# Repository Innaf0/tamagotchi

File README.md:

# tamagotchi
I made a tamagotchi using a guide so i wouldnt really call it my own, if anyone doesnt know whats a tamagotchi i suggest u look it up or in short a tamagotchi is a virtual pet which u have to feed and play with or else it'll get sad just like with real life pets:D
I made this tamagotchi Jinx inspired bc i really like Arcane, my pcb and case both have Jinx inspired drawings

and here's the rendered case which will be transparent so my art could be seen:3

heres my ZINE page

I made this project to learn the basics of hardware
this is my very first hardware project so thats why i decided to follow a guide instead of straight up jumping in to smth i didnt even know how to handle, this is my 2nd or maybe 3rd read.me so tbh idk if this is any good but anyways;)

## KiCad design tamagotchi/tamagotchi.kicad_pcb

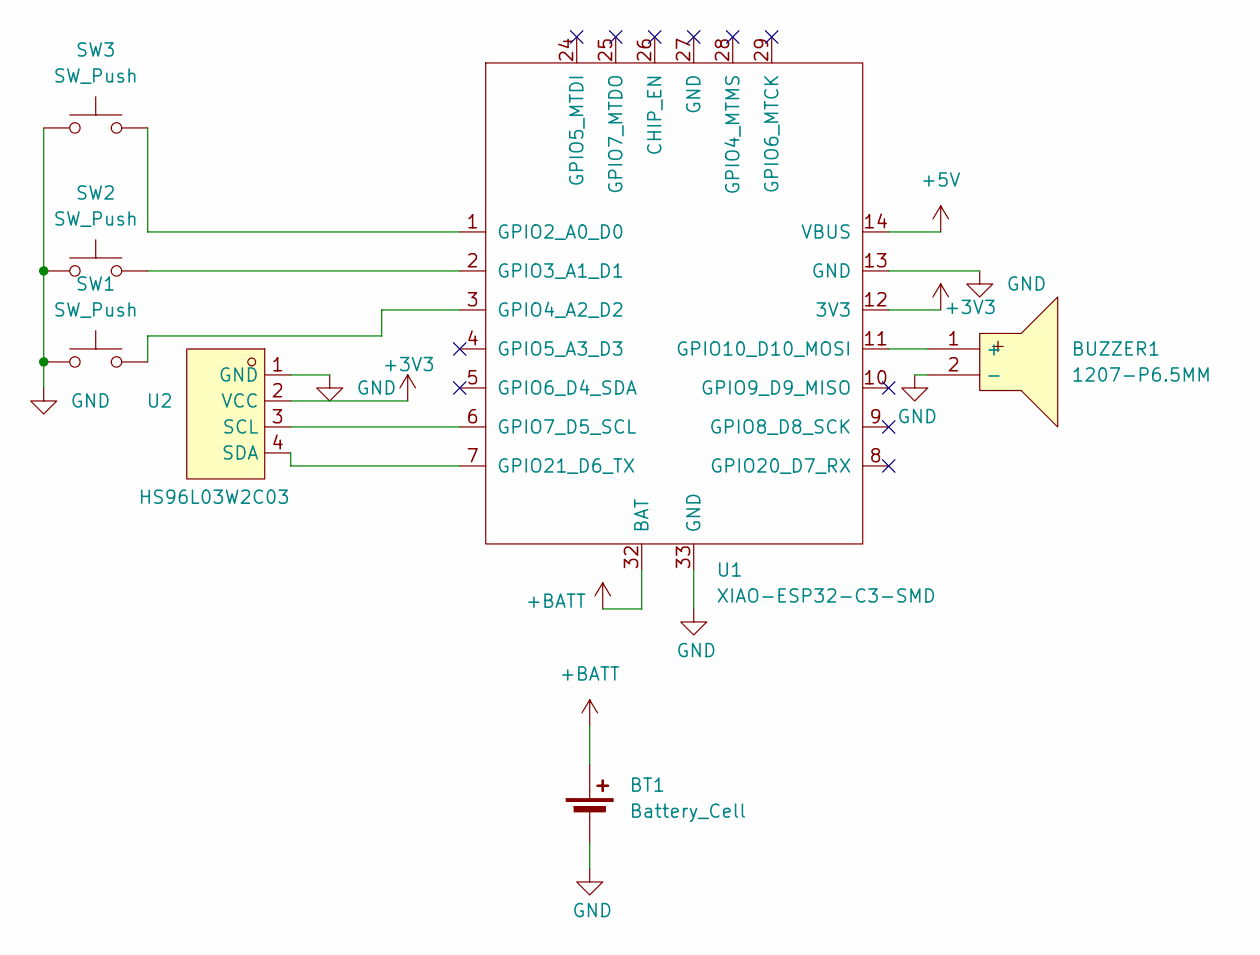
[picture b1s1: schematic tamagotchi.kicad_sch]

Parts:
BT1: Battery_Cell; PinHeader_1x02_P2.54mm_Vertical
BUZZER1: 1207-P6.5MM; Buzzer_12x9.5RM7.6; MPN 1207-P6.5MM; LCSC Part C49246964
SW1, SW2, SW3: SW_Push; SW-TH_4P-L4.5-W4.5-P3.00-LS4.8
U1: XIAO-ESP32-C3-SMD; XIAO-ESP32-C3-DIP-SMD
U2: HS96L03W2C03; OLED-TH_L27.8-W27.2-P2.54_C9900033791; MPN HS96L03W2C03; LCSC Part C5248080

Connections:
+3V3: U1.12 (3V3), U2.2 (VCC)
+5V: U1.14 (VBUS)
+BATT: BT1.1 (+), U1.32 (BAT)
GND: BT1.2 (-), BUZZER1.2 (-), SW1.1, SW2.1, SW3.1, U1.13 (GND), U1.33 (GND), U2.1 (GND)
unnamed: BUZZER1.1 (+), U1.11 (GPIO10_D10_MOSI)
unnamed: SW3.2, U1.1 (GPIO2_A0_D0)
unnamed: SW2.2, U1.2 (GPIO3_A1_D1)
unnamed: SW1.2, U1.3 (GPIO4_A2_D2)
unnamed: U1.6 (GPIO7_D5_SCL), U2.3 (SCL)
unnamed: U1.7 (GPIO21_D6_TX), U2.4 (SDA)

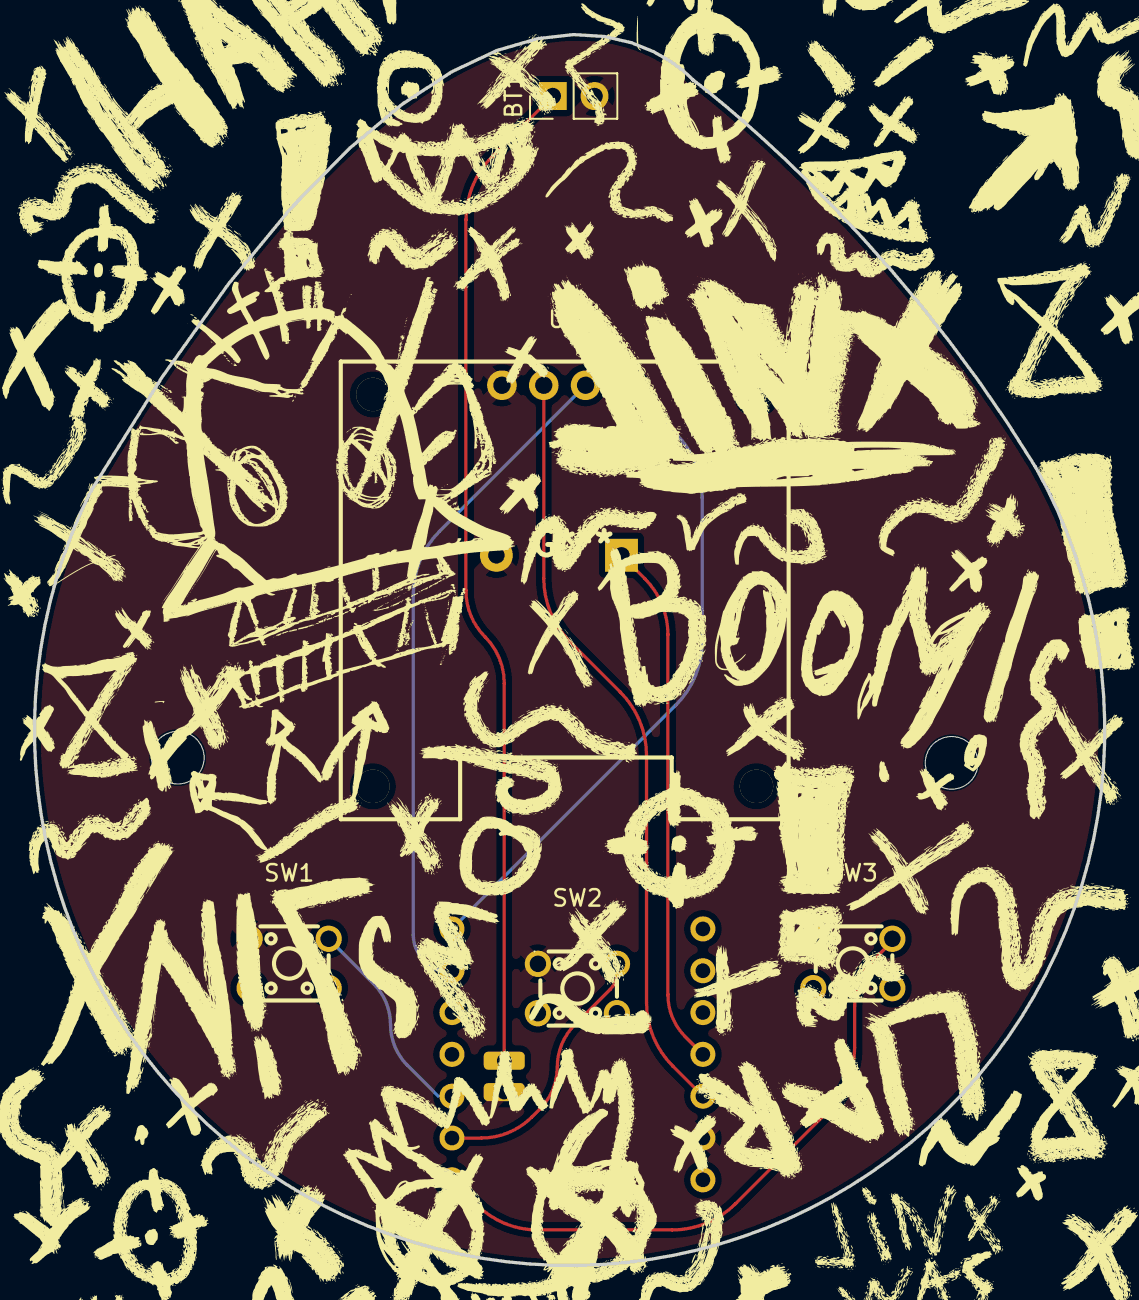
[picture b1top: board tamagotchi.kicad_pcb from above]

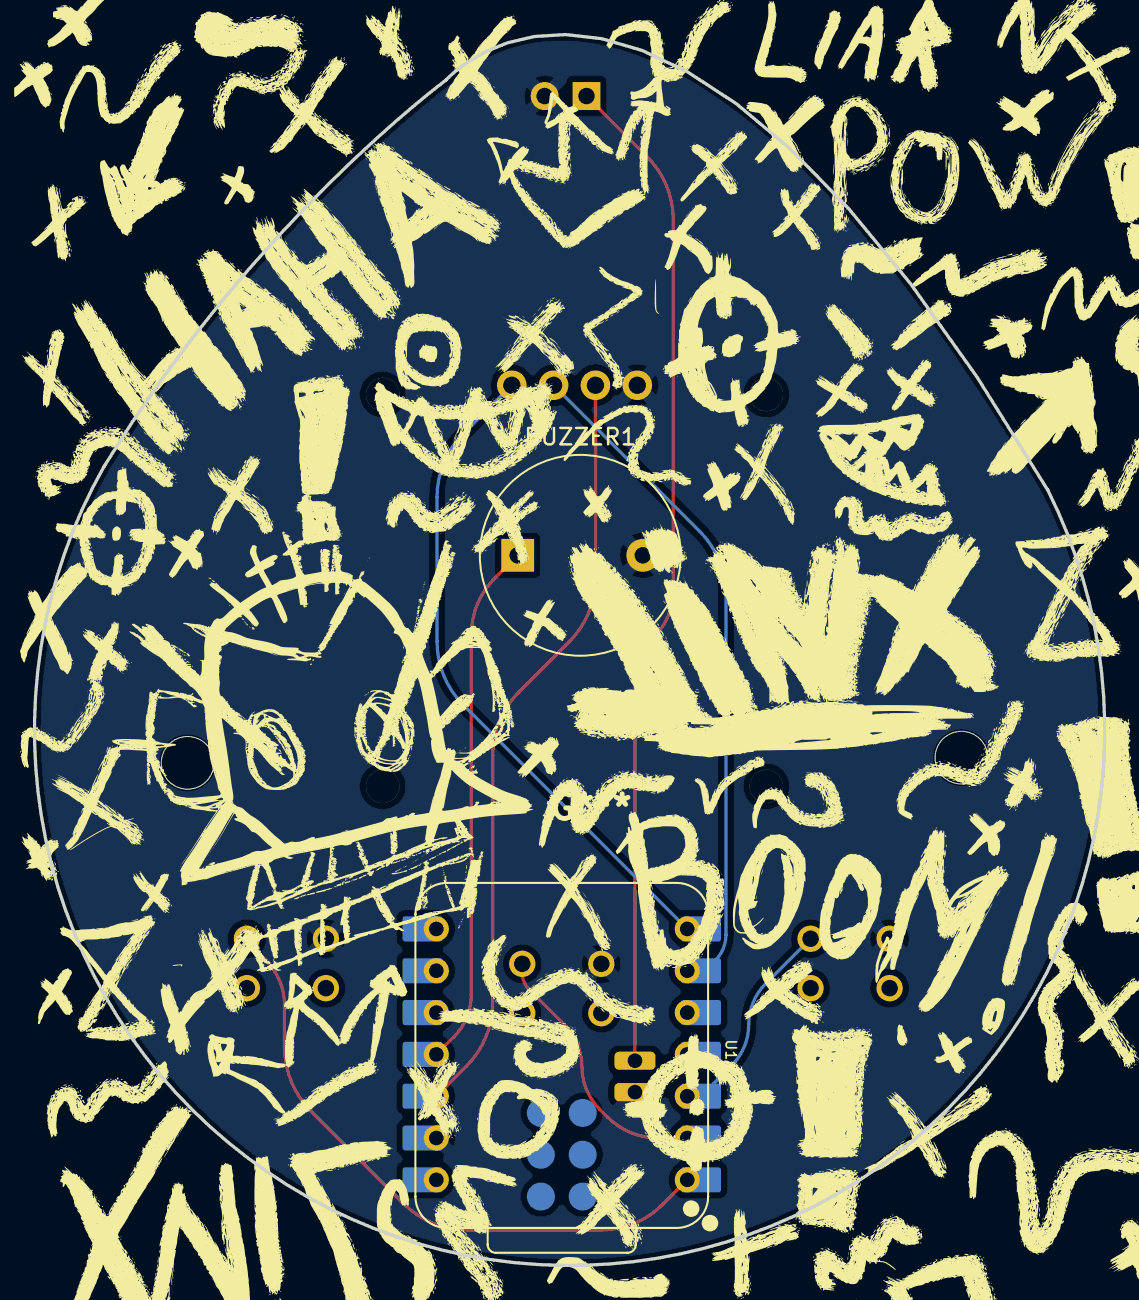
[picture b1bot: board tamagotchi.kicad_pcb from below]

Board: 2 copper layers, 65.0 x 74.8 mm, 7 parts (2 on the bottom side), 9 nets.

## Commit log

2026-04-24 finished schematic
    tamagotchi
2026-05-29 added blender
2026-05-30 finished rendering/blendering
2026-05-31 Enhance README with project details and images
    Expanded project description and added images.
2026-05-31 finished up my project
2026-05-31 added my ZINE page
2026-05-31 Update README with ZINE page section
    Added a new section for the ZINE page with an image.
2026-05-31 Update README with project learning objectives
    Added a project description to the README.
2026-05-31 fixed my requirements
